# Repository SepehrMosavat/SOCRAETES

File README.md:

## SOCRAETES: SOlar Cells Recorded And EmulaTed EaSily

**Sayedsepehr Mosavat, Matteo Zella, Pedro José Marrón**  
**Networked Embedded Systems Group (NES) - Universität Duisburg-Essen**

SOCRAETES is a tool for supporting the design and evaluation of energy harvesting
systems. The core idea behind the development of SOCRAETES has been to
enable easy replication of the required hardware components, therefore
decreasing the entry-barrier into this field of research, even for researchers
and hobbyists that have little prior experience with electronics. This is
achieved by simplifying the hardware design as much as possible, and also by
employing only through-hole components in the required hardware.

The hardware design of SOCRAETES provides a high level of flexibility in terms
of the range of measurements and emulations. Since there is a tradeoff between
this range and the overall accuracy of the system, the users have the
possibility of modifying the underlying hardware by using different passive
components. By doing so, each user can target the best overall range of
measurements and emulation, while also achieving a high level of accuracy.

Please refer to our demo abstract, presented at EWSN 2021, for more information
regarding the design and implementation of SOCRAETES.

To use SOCRAETES, the following prerequisites exist:
- SOCRAETES hardware, either assembled on a prototyping board, or optionally,
using the PCB found in the hardware directory. Please note that the full
functionality of SOCRAETES can be realized using prototyping boards, but the
highest reliability and accuracy will be achieved only if the PCB is used.
Please refer to the hardware directory for instructions regarding preparing the
hardware
- SOCRAETES firmware, which will be running on a Teensy 3.6. Please refer to
the firmware directory for instructions on flashing the Teensy board.
- SOCRAETES software, which will be running on a host PC and used for
acquiring data and emulating traces. The current implementation of SOCRAETES
is using Python code, but we are working on extensions of this functionality
for further data visualization and analysis.

#### Contact us
In case you experience any issues while using SOCRAETES, or have any questions
or ideas for further improvements, please do not hesitate to contact us via
e-mail! You can find our contact information on our [web page](https://nes.uni-due.de).

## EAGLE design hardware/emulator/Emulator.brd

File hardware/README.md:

## SOCRAETES: SOlar Cells Recorded And EmulaTed EaSily

This document provides instructions for replicating the hardware of SOCRAETES.
As far as the hardware is concerned, there are 2 options for the users:
1. Using either a solderless breadboard or prototyping board (perfboard)
2. Using the SOCRAETES PCB

The SOCRAETES hardware could be implemented on a solderless breadboard, but this
is highly unrecommended, since the parasitic capacitance and inductance imposed
by a solderless breadboard will very likely interfere with the measurements and
the trace emulation. This will, in turn, reduce the overall accuracy and reliability
of the hardware. However, the SOCRAETES hardware can be implemented quite reliably
on a so-called *Perfboard*. In comparison to a solderless breadboard, a
perfboard will not only provide superior mechanical support to the components,
but also lower parasitic effects that could hinder the accuracy of the hardware.

Aside from the options mentioned above, the SOCRAETES hardware can also be
implemented on the dedicated PCB found in the hardware directory. This method will
yield the highest reliability and accuracy of the hardware, and therefore, is
the recommended method of replicating the hardware.

Regardless of the method chosen for implementing the SOCRAETES hardware, since
all of the components are available in through-hole packages, the soldering of
the hardware should not be a great challenge, even for the users with little
prior experience in electronics and soldering.

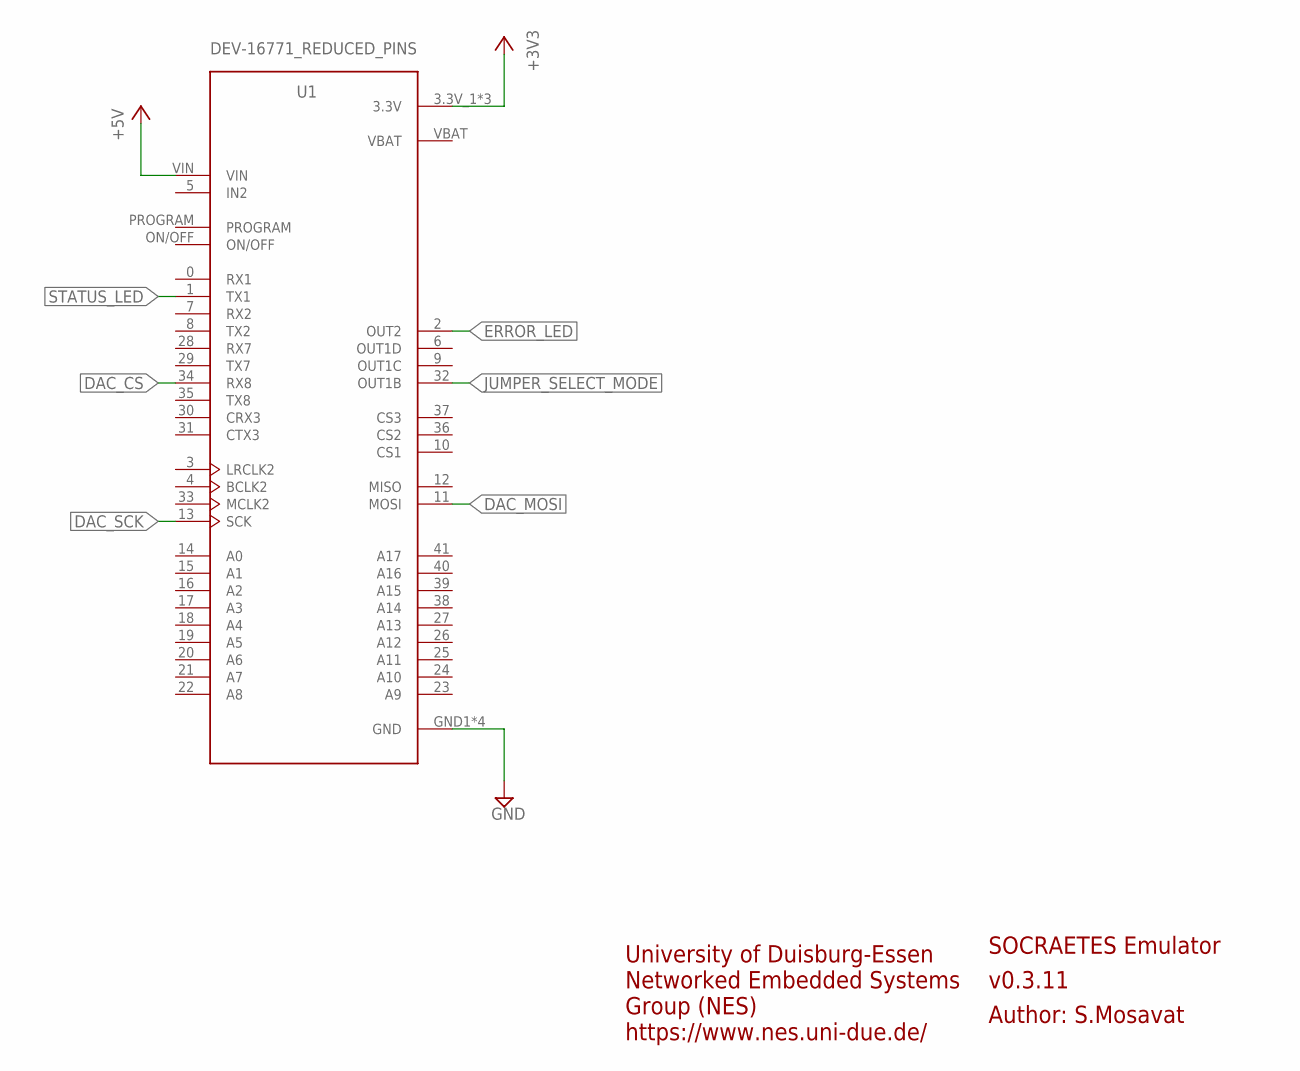
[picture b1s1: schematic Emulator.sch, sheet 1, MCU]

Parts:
U1: DEV-16771_REDUCED_PINS; MODULE_DEV-16771_REDUCED_PINS

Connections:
+3V3: U1.3.3V_1 (3.3V), U1.3.3V_2 (3.3V), U1.3.3V_3 (3.3V); also elsewhere on the board
+5V: U1.VIN; also elsewhere on the board
DAC_CS: U1.34 (RX8); also elsewhere on the board
DAC_MOSI: U1.11 (MOSI); also elsewhere on the board
DAC_SCK: U1.13 (SCK); also elsewhere on the board
ERROR_LED: U1.2 (OUT2); also elsewhere on the board
GND: U1.GND1 (GND), U1.GND2 (GND), U1.GND3 (GND), U1.GND4 (GND); also elsewhere on the board
JUMPER_SELECT_MODE: U1.32 (OUT1B); also elsewhere on the board
STATUS_LED: U1.1 (TX1); also elsewhere on the board

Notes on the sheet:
SOCRAETES Emulator
v0.3.11
Author: S.Mosavat
University of Duisburg-Essen Networked Embedded Systems Group (NES) https://www.nes.uni-due.de/

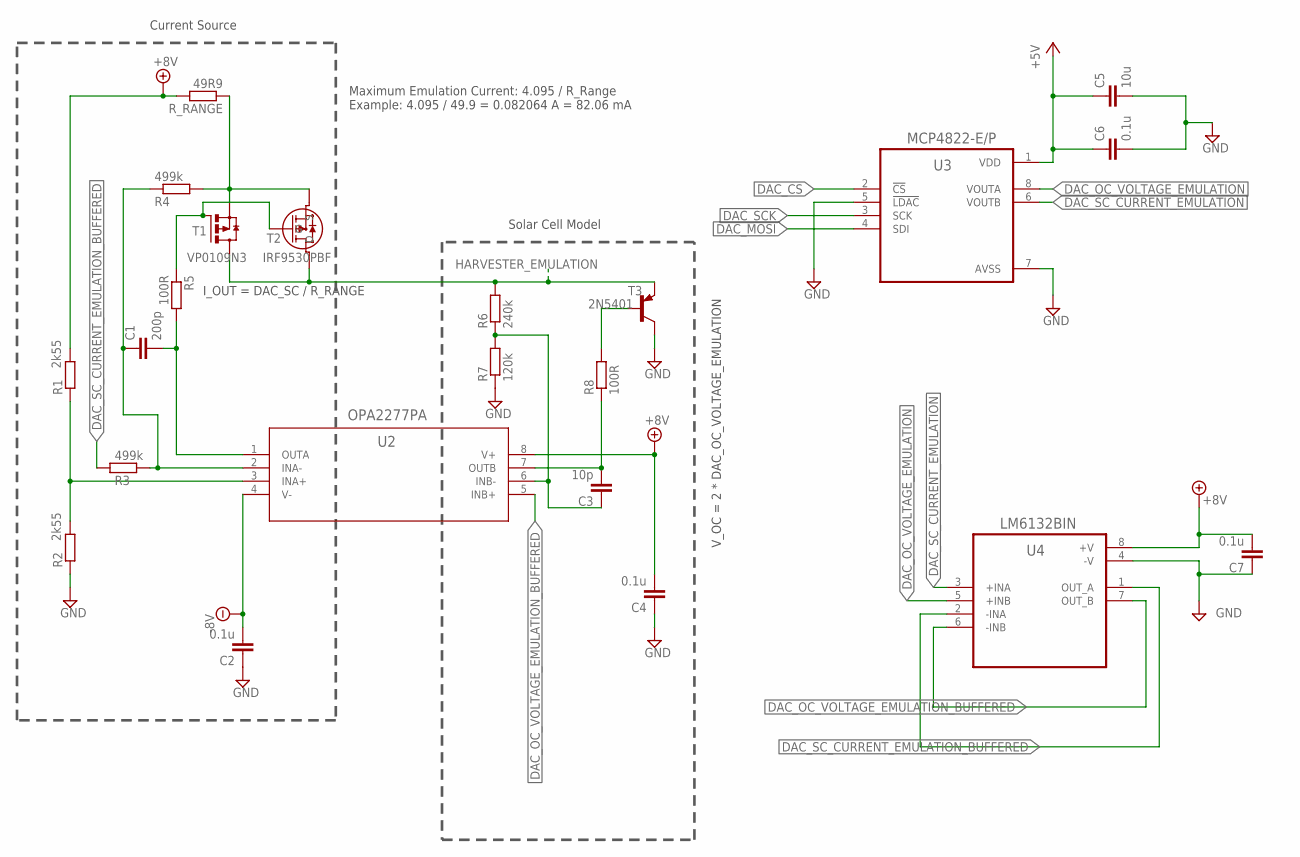
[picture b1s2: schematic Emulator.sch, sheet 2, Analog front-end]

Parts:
C1: 200p; C025-024X044
C2, C4, C6, C7: 0.1u; C025-024X044
C3: 10p; C025-024X044
C5: 10u; C025-024X044
R1, R2: 2k55; 0207/10
R3, R4: 499k; 0207/10
R5, R8: 100R; 0207/10
R6: 240k; 0207/10
R7: 120k; 0207/10
R_RANGE: 49R9; 0207/10
T1: VP0109N3; TO92-SGD
T2: IRF9530PBF; TO220AB_VIS
T3: 2N5401; TO92-EBC
U2: OPA2277PA; P8
U3: MCP4822-E/P; DIP787W46P254L927H533Q8
U4: LM6132BIN; DIP794W45P254L959H508Q8

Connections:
+5V: C5.1, C6.1, U3.1 (VDD); also elsewhere on the board
+8V: C4.2, C7.2, R1.2, R_RANGE.2, U2.8 (V+), U4.8 (+V); also elsewhere on the board
-8V: C2.2, U2.4 (V-); also elsewhere on the board
DAC_CS: U3.2 (!CS); also elsewhere on the board
DAC_MOSI: U3.4 (SDI); also elsewhere on the board
DAC_OC_VOLTAGE_EMULATION: U3.8 (VOUTA), U4.5 (+INB)
DAC_OC_VOLTAGE_EMULATION_BUFFERED: U2.5 (INB+), U4.6 (-INB), U4.7 (OUT_B)
DAC_SCK: U3.3 (SCK); also elsewhere on the board
DAC_SC_CURRENT_EMULATION: U3.6 (VOUTB), U4.3 (+INA)
DAC_SC_CURRENT_EMULATION_BUFFERED: R3.2, U4.1 (OUT_A), U4.2 (-INA)
GND: C2.1, C4.1, C5.2, C6.2, C7.1, R2.1, R7.1, T3.C, U3.5 (!LDAC), U3.7 (AVSS), U4.4 (-V); also elsewhere on the board
HARVESTER_EMULATION: R6.2, T1.DRAIN (D), T2.D, T3.E; also elsewhere on the board
unnamed: R1.1, R2.2, U2.3 (INA+)
unnamed: C1.1, R3.1, R4.2, U2.2 (INA-)
unnamed: R5.1, T1.GATE (G), T2.G
unnamed: C1.2, R5.2, U2.1 (OUTA)
unnamed: R4.1, R_RANGE.1, T1.SOURCE (S), T2.S
unnamed: C3.1, R6.1, R7.2, U2.6 (INB-)
unnamed: R8.2, T3.B
unnamed: C3.2, R8.1, U2.7 (OUTB)

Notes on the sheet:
Current Source
Solar Cell Model
Maximum Emulation Current: 4.095 / R_Range Example: 4.095 / 49.9 = 0.082064 A = 82.06 mA
I_OUT = DAC_SC / R_RANGE
V_OC = 2 * DAC_OC_VOLTAGE_EMULATION

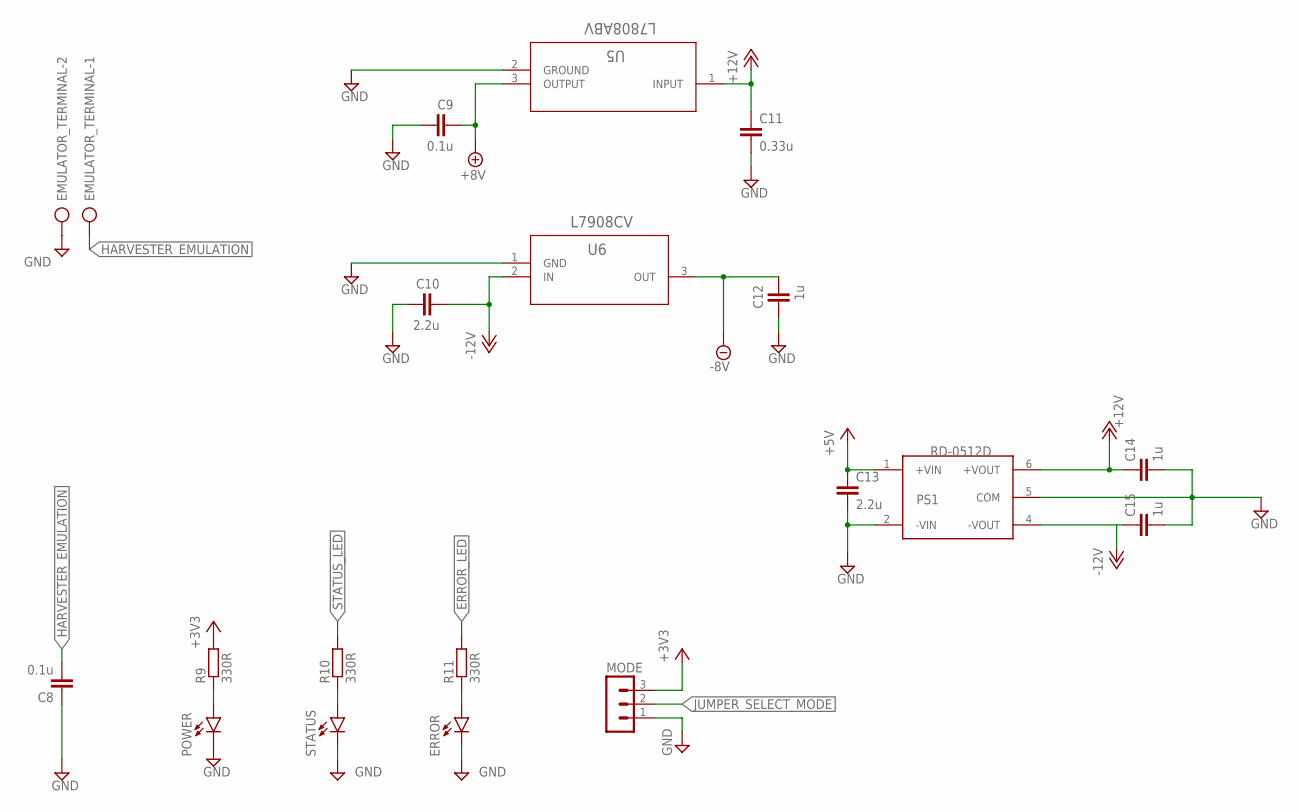
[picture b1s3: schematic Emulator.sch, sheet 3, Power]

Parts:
C8, C9: 0.1u; C025-024X044
C10, C13: 2.2u; C025-024X044
C11: 0.33u; C025-024X044
C12, C14, C15: 1u; C025-024X044
EMULATOR_TERMINAL: AK300/2
ERROR: LED5MM
MODE: MA03-1
POWER: LED5MM
PS1: RD-0512D; CONV_RD-0512D
R9, R10, R11: 330R; 0207/10
STATUS: LED5MM
U5: L7808ABV; TO-220_STM
U6: L7908CV; TO-220_STM

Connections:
+3V3: MODE.3, R9.2; also elsewhere on the board
+5V: C13.1, PS1.1 (+VIN); also elsewhere on the board
+8V: C9.2, U5.3 (OUTPUT); also elsewhere on the board
+12V: C11.1, C14.1, PS1.6 (+VOUT), U5.1 (INPUT)
-8V: C12.2, U6.3 (OUT); also elsewhere on the board
-12V: C10.2, C15.1, PS1.4 (-VOUT), U6.2 (IN)
ERROR_LED: R11.2; also elsewhere on the board
GND: C8.1, C9.1, C10.1, C11.2, C12.1, C13.2, C14.2, C15.2, EMULATOR_TERMINAL.2, ERROR.K (C), MODE.1, POWER.K (C), PS1.2 (-VIN), PS1.5 (COM), STATUS.K (C), U5.2 (GROUND), U6.1 (GND); also elsewhere on the board
HARVESTER_EMULATION: C8.2, EMULATOR_TERMINAL.1; also elsewhere on the board
JUMPER_SELECT_MODE: MODE.2; also elsewhere on the board
unnamed: R10.1, STATUS.A
unnamed: ERROR.A, R11.1
unnamed: POWER.A, R9.1
STATUS_LED: R10.2; also elsewhere on the board

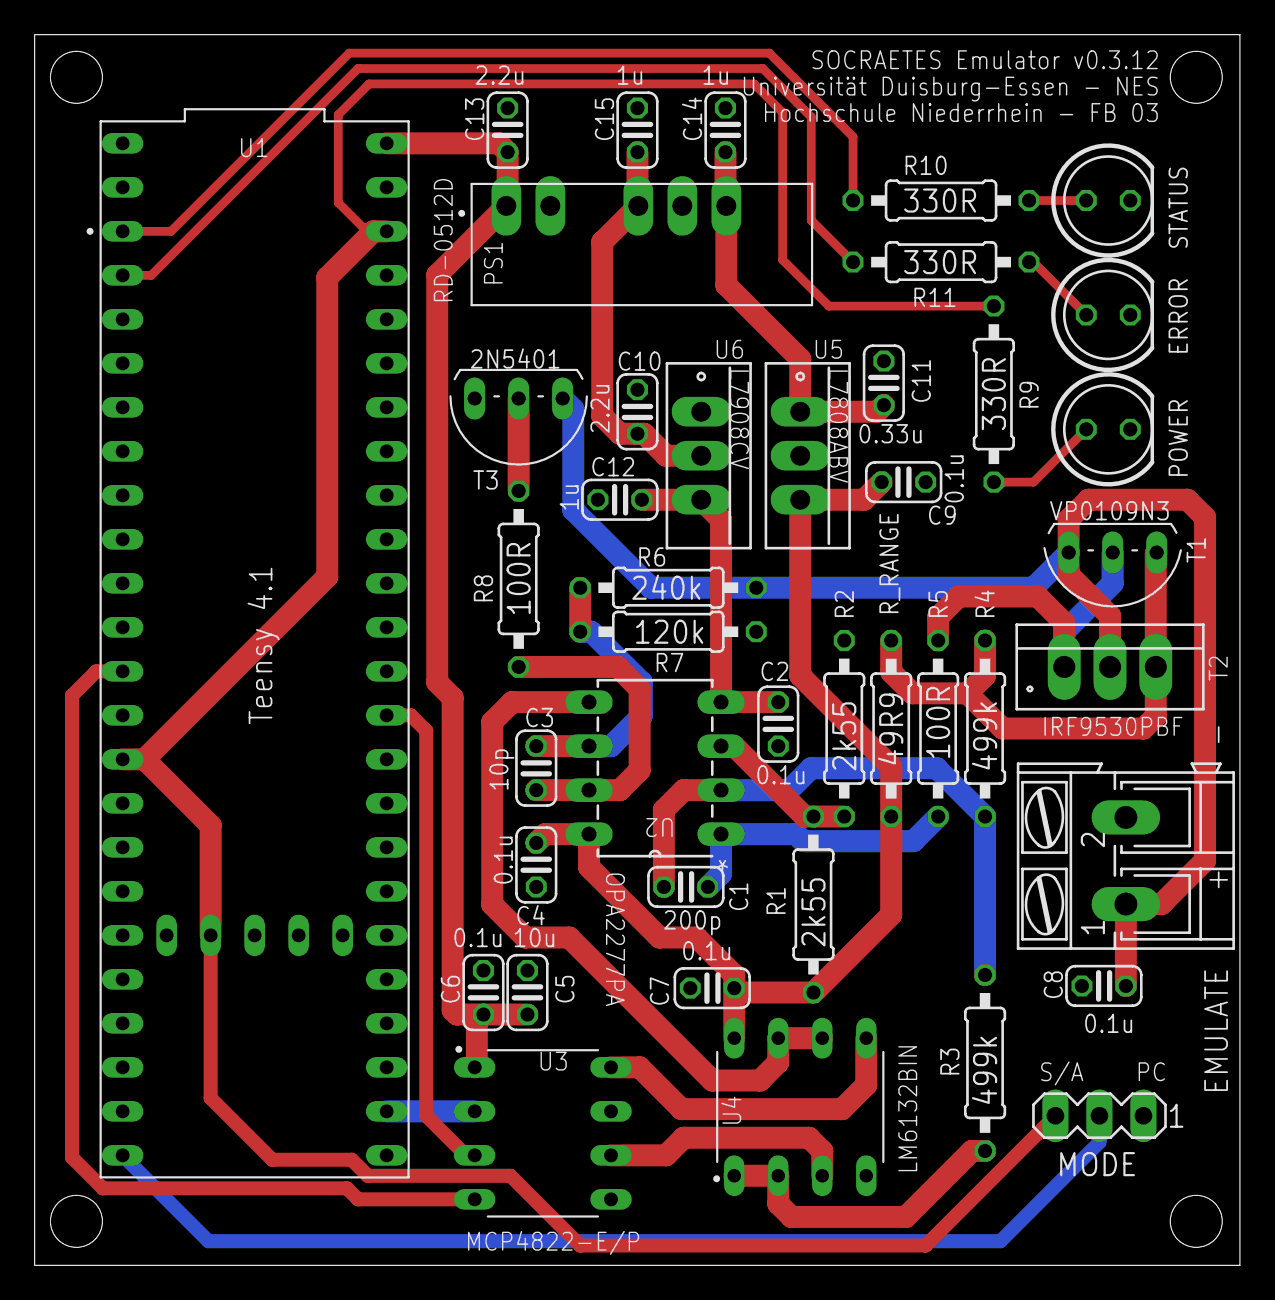
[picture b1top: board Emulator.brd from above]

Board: 2 copper layers, 69.6 x 71.0 mm, 42 parts (0 on the bottom side), 29 nets.

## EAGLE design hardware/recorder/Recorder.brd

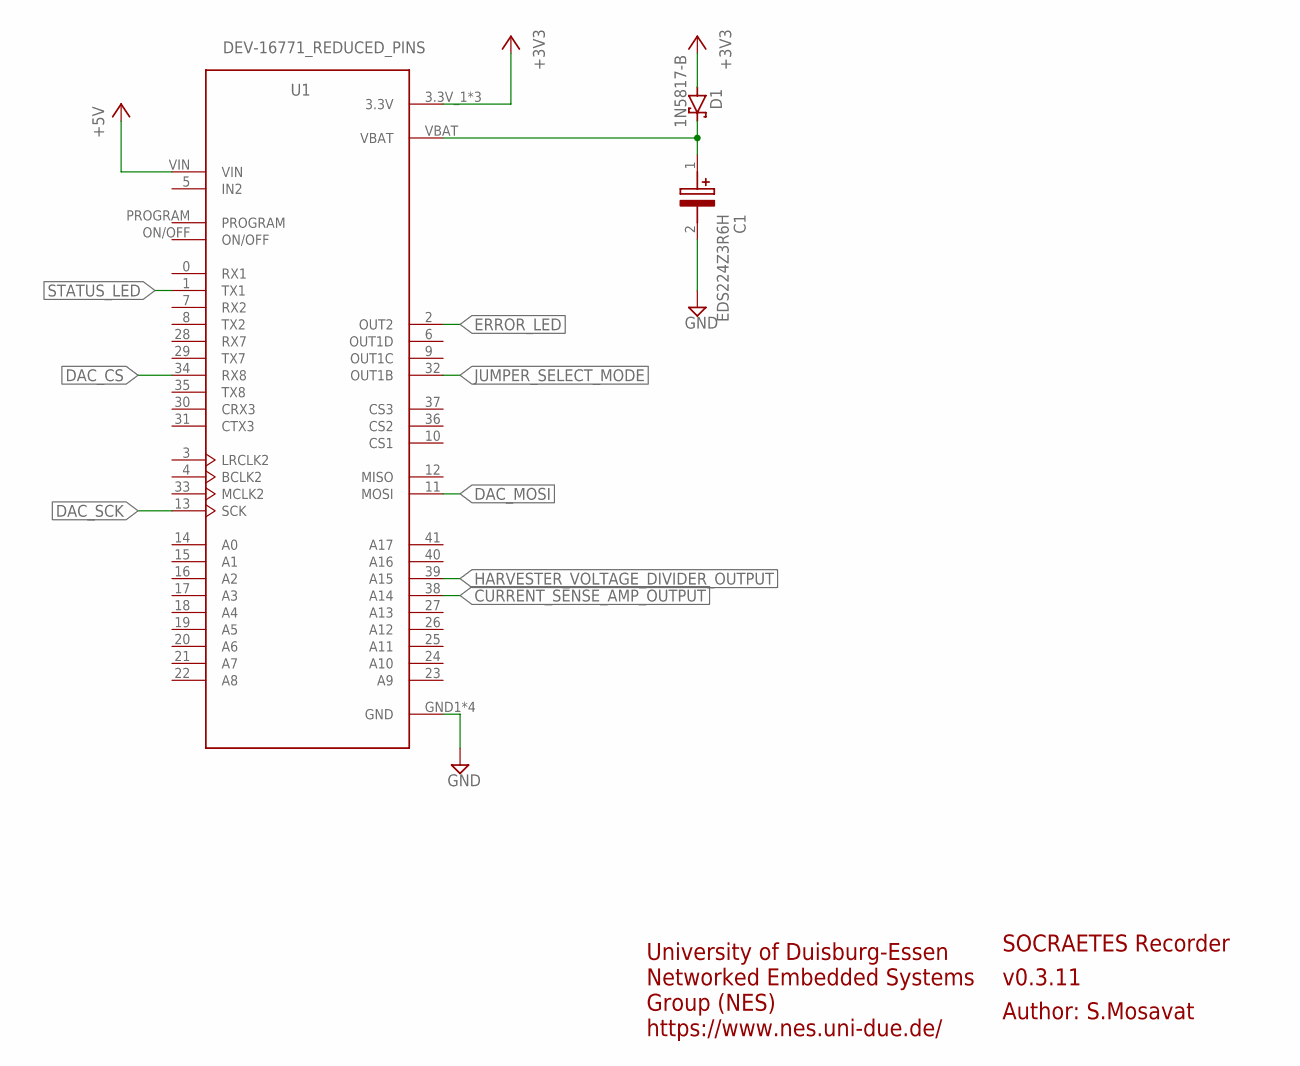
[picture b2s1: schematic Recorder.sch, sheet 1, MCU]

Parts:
C1: EDS224Z3R6H
D1: 1N5817-B; DO41-7.6
U1: DEV-16771_REDUCED_PINS; MODULE_DEV-16771_REDUCED_PINS

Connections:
+3V3: D1.A, U1.3.3V_1 (3.3V), U1.3.3V_2 (3.3V), U1.3.3V_3 (3.3V); also elsewhere on the board
+5V: U1.VIN; also elsewhere on the board
CURRENT_SENSE_AMP_OUTPUT: U1.38 (A14); also elsewhere on the board
DAC_CS: U1.34 (RX8); also elsewhere on the board
DAC_MOSI: U1.11 (MOSI); also elsewhere on the board
DAC_SCK: U1.13 (SCK); also elsewhere on the board
ERROR_LED: U1.2 (OUT2); also elsewhere on the board
GND: C1.2 (-), U1.GND1 (GND), U1.GND2 (GND), U1.GND3 (GND), U1.GND4 (GND); also elsewhere on the board
HARVESTER_VOLTAGE_DIVIDER_OUTPUT: U1.39 (A15); also elsewhere on the board
JUMPER_SELECT_MODE: U1.32 (OUT1B); also elsewhere on the board
unnamed: C1.1 (+), D1.C, U1.VBAT
STATUS_LED: U1.1 (TX1); also elsewhere on the board

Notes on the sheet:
SOCRAETES Recorder
v0.3.11
Author: S.Mosavat
University of Duisburg-Essen Networked Embedded Systems Group (NES) https://www.nes.uni-due.de/

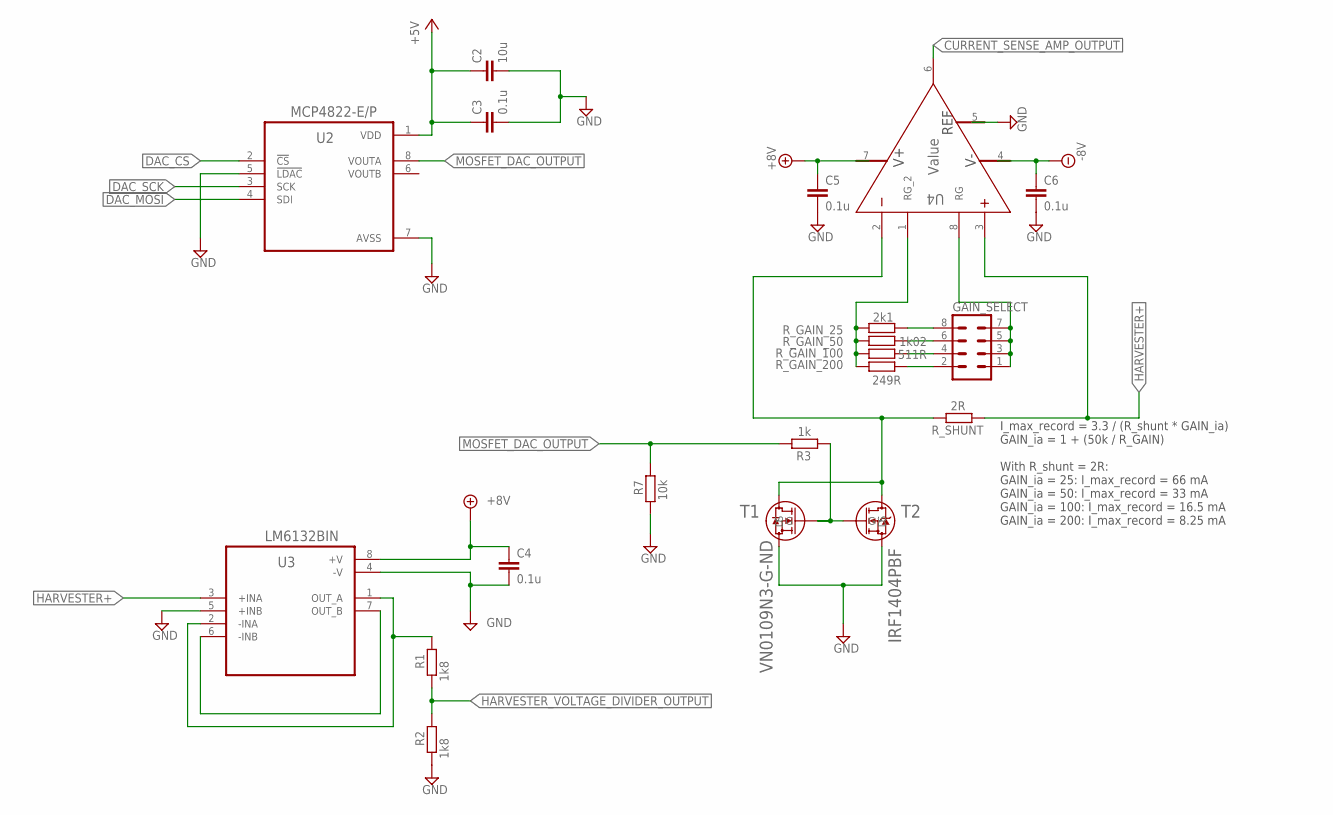
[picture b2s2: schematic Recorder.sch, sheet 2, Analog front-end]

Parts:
C2: 10u; C025-024X044
C3, C4, C5, C6: 0.1u; C025-024X044
GAIN_SELECT: MA04-2
R1, R2: 1k8; 0207/10
R3: 1k; 0207/10
R7: 10k; 0207/10
R_GAIN_25: 2k1; 0207/10
R_GAIN_50: 1k02; 0207/10
R_GAIN_100: 511R; 0207/10
R_GAIN_200: 249R; 0207/10
R_SHUNT: 2R; 0207/10
T1: VN0109N3-G-ND; TO92-CBE
T2: IRF1404PBF; PG-TO220-3-904_INF
U2: MCP4822-E/P; DIP787W46P254L927H533Q8
U3: LM6132BIN; DIP794W45P254L959H508Q8
U4: Value; P0008A

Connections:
+5V: C2.1, C3.1, U2.1 (VDD); also elsewhere on the board
+8V: C4.1, C5.1, U3.8 (+V), U4.7 (V+); also elsewhere on the board
-8V: C6.1, U4.4 (V-); also elsewhere on the board
CURRENT_SENSE_AMP_OUTPUT: U4.6 (OUT); also elsewhere on the board
DAC_CS: U2.2 (!CS); also elsewhere on the board
DAC_MOSI: U2.4 (SDI); also elsewhere on the board
DAC_SCK: U2.3 (SCK); also elsewhere on the board
GND: C2.2, C3.2, C4.2, C5.2, C6.2, R2.1, R7.1, T1.SOURCE (S), T2.S, U2.5 (!LDAC), U2.7 (AVSS), U3.4 (-V), U3.5 (+INB), U4.5 (REF); also elsewhere on the board
HARVESTER+: R_SHUNT.1, U3.3 (+INA), U4.3 (IN+); also elsewhere on the board
HARVESTER_VOLTAGE_DIVIDER_OUTPUT: R1.1, R2.2; also elsewhere on the board
MOSFET_DAC_OUTPUT: R3.2, R7.2, U2.8 (VOUTA)
unnamed: GAIN_SELECT.8, R_GAIN_25.1
unnamed: GAIN_SELECT.6, R_GAIN_50.1
unnamed: U3.6 (-INB), U3.7 (OUT_B)
unnamed: R_SHUNT.2, T1.DRAIN (D), T2.D, U4.2 (IN-)
unnamed: R1.2, U3.1 (OUT_A), U3.2 (-INA)
unnamed: GAIN_SELECT.4, R_GAIN_100.1
unnamed: R3.1, T1.GATE (G), T2.G
unnamed: R_GAIN_25.2, R_GAIN_50.2, R_GAIN_100.2, R_GAIN_200.2, U4.1 (RG_2)
unnamed: GAIN_SELECT.1, GAIN_SELECT.3, GAIN_SELECT.5, GAIN_SELECT.7, U4.8 (RG)
unnamed: GAIN_SELECT.2, R_GAIN_200.1

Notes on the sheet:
I_max_record = 3.3 / (R_shunt * GAIN_ia) GAIN_ia = 1 + (50k / R_GAIN) With R_shunt = 2R: GAIN_ia = 25: I_max_record = 66 mA GAIN_ia = 50: I_max_record = 33 mA GAIN_ia = 100: I_max_record = 16.5 mA GAIN_ia = 200: I_max_record = 8.25 mA

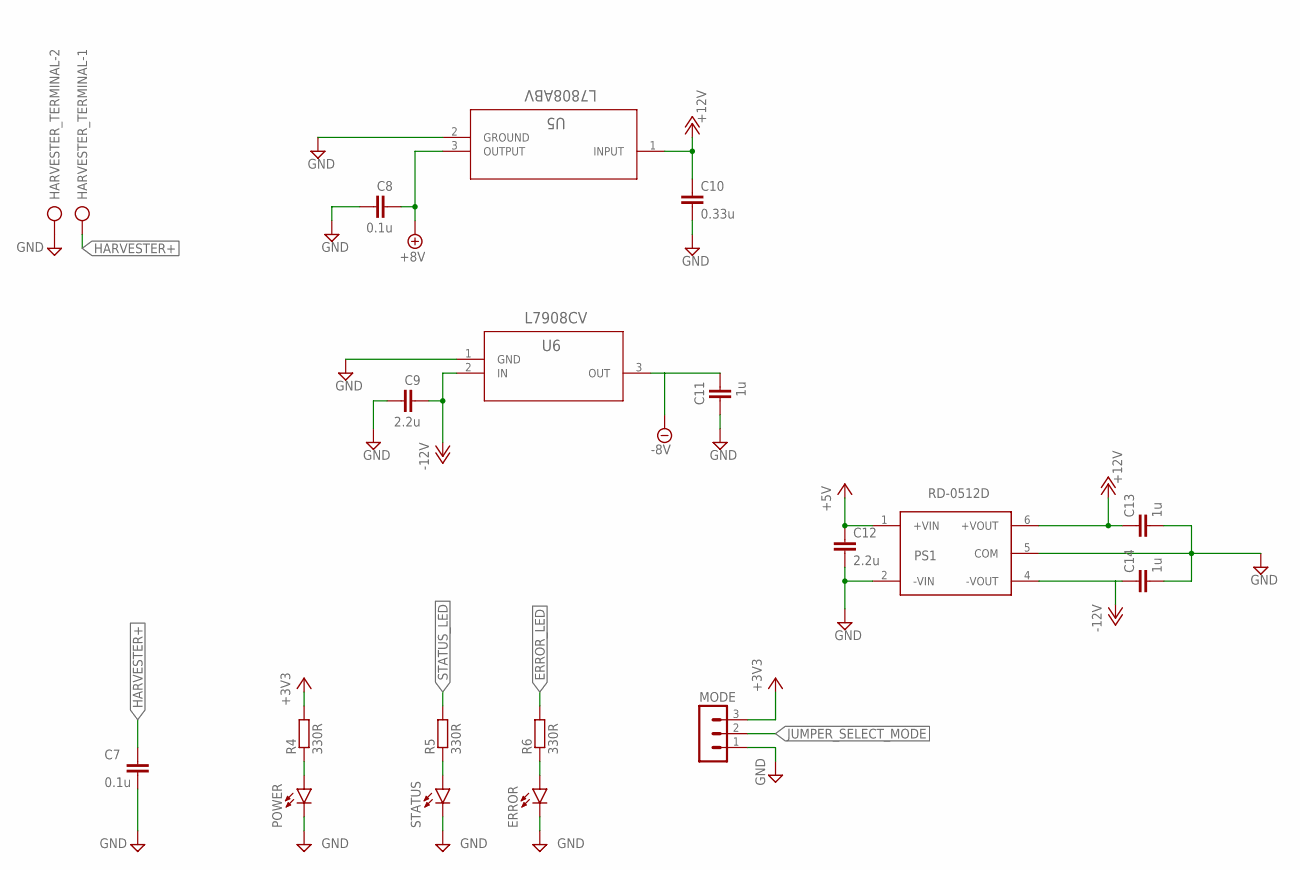
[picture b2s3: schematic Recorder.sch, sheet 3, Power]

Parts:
C7, C8: 0.1u; C025-024X044
C9, C12: 2.2u; C025-024X044
C10: 0.33u; C025-024X044
C11, C13, C14: 1u; C025-024X044
ERROR: LED5MM
HARVESTER_TERMINAL: AK300/2
MODE: MA03-1
POWER: LED5MM
PS1: RD-0512D; CONV_RD-0512D
R4, R5, R6: 330R; 0207/10
STATUS: LED5MM
U5: L7808ABV; TO-220_STM
U6: L7908CV; TO-220_STM

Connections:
+3V3: MODE.3, R4.2; also elsewhere on the board
+5V: C12.1, PS1.1 (+VIN); also elsewhere on the board
+8V: C8.2, U5.3 (OUTPUT); also elsewhere on the board
+12V: C10.1, C13.1, PS1.6 (+VOUT), U5.1 (INPUT)
-8V: C11.2, U6.3 (OUT); also elsewhere on the board
-12V: C9.2, C14.1, PS1.4 (-VOUT), U6.2 (IN)
ERROR_LED: R6.2; also elsewhere on the board
GND: C7.2, C8.1, C9.1, C10.2, C11.1, C12.2, C13.2, C14.2, ERROR.K (C), HARVESTER_TERMINAL.2, MODE.1, POWER.K (C), PS1.2 (-VIN), PS1.5 (COM), STATUS.K (C), U5.2 (GROUND), U6.1 (GND); also elsewhere on the board
HARVESTER+: C7.1, HARVESTER_TERMINAL.1; also elsewhere on the board
JUMPER_SELECT_MODE: MODE.2; also elsewhere on the board
unnamed: ERROR.A, R6.1
unnamed: R5.1, STATUS.A
unnamed: POWER.A, R4.1
STATUS_LED: R5.2; also elsewhere on the board

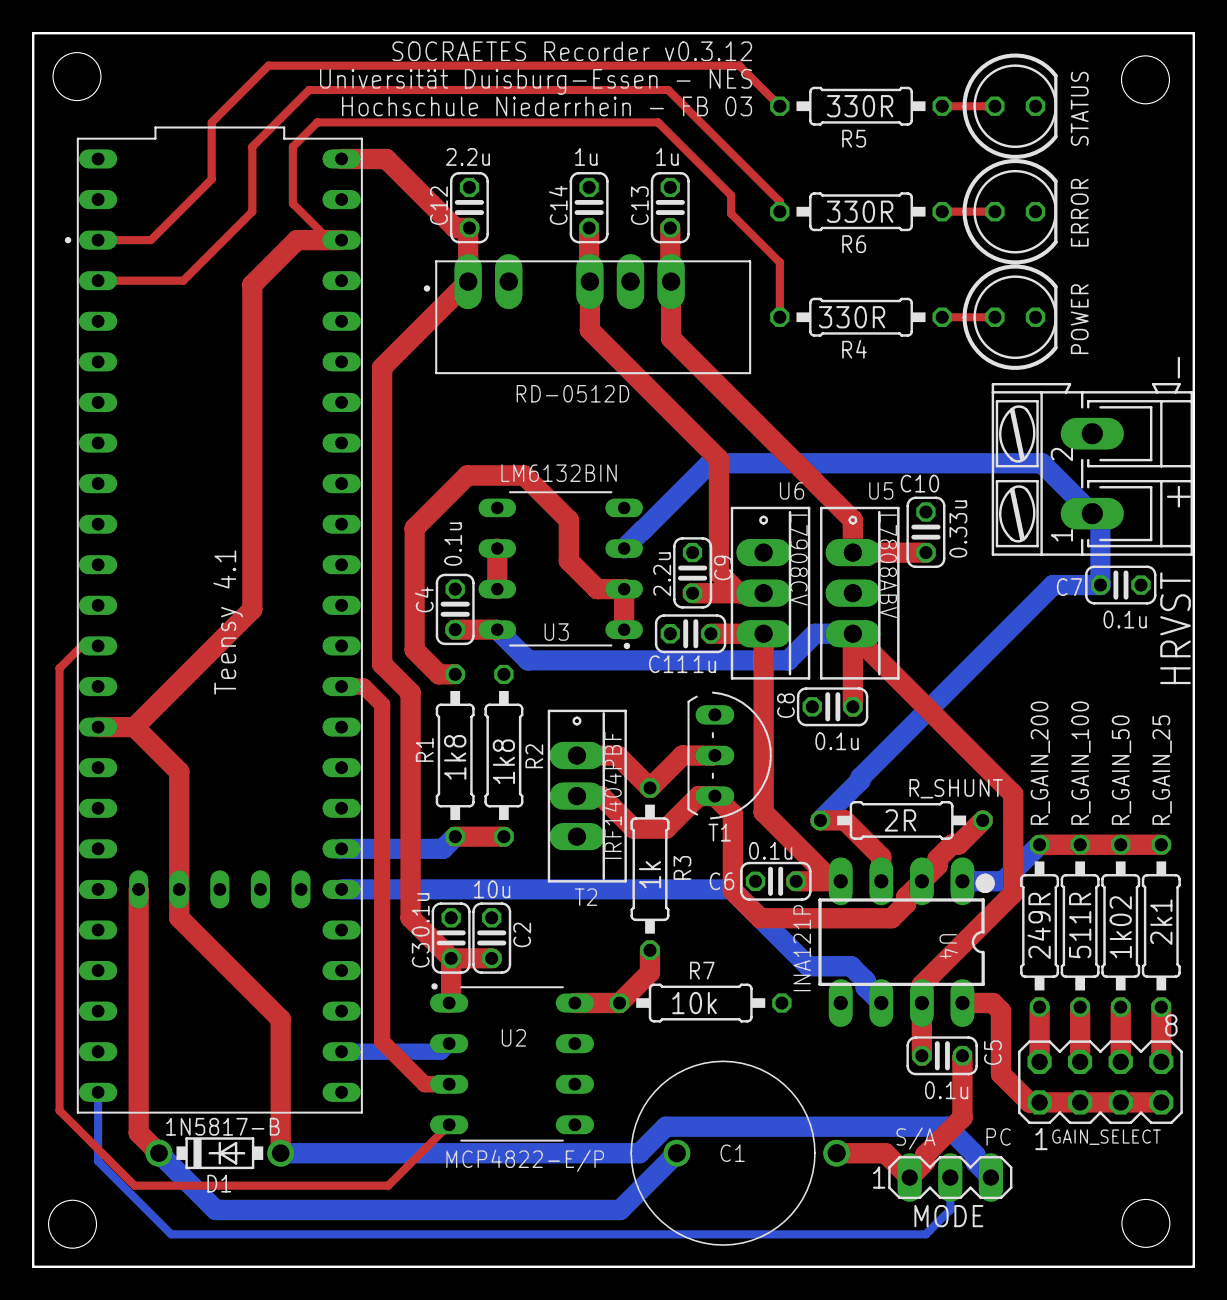
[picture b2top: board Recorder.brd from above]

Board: 2 copper layers, 72.6 x 77.2 mm, 42 parts (0 on the bottom side), 31 nets.

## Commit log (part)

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2020-09-17 Update gitignore
2020-09-17 Add microcontroller firmware files
2020-09-17 Add software files
2020-09-17 Add hardware readme file
2020-09-17 Move solar cell recorder files to a separate folder
2020-09-17 Update ADC reference voltage definition
2020-09-17 Increase PGA's gain used for current measurement
2020-09-17 Add class member for the number of points in each curve
2020-09-17 Decrease PGA's gain used for current measurement to avoid saturation issues at high currents
2020-09-17 Add delay after writing a new value to the potentiometer
2020-09-17 Refactor code
2020-09-17 Change the number of captured points in each curve
2020-09-17 Stop tracking IDE files
2020-09-17 Change the path of recorded traces to a separate directory
2020-09-17 Remove delay to achieve higher capture speed
2020-09-17 Specify data type in the HDF5 file containing the captured traces
2020-09-17 Add class for describing the energy harvesting conditions
2020-09-17 Add a feature for automated filename generation
2020-09-18 Add TODO
2020-09-18 Add return type to the function
2020-09-18 Add error checking for empty folder
2020-09-18 Add the start date and time of data capturing to the harvesting condition
2020-09-21 Add the end time of data capturing to the harvesting condition
2020-09-25 Add check for negative ADC readings for current and voltage calculations
2020-10-01 Add/edit readme files
2020-10-01 Dynamically update the plot range
2020-10-15 Remove DAC and rotary encoder from the current project
2020-10-15 Replace digital potentiometer as system load with a MOSFET controlled by the DAC
2020-10-15 Add function for updating the MOSFET load on each main loop iteration
2020-10-15 Change the value of the resistors in the voltage divider used for measuring the harvester voltage
2020-10-15 Reduce ADC resolution
2020-10-15 Modify ADC settings for improving the quality of current/voltage measurements
2020-10-15 Update definitions used in function implementation
2020-10-15 Remove PGA gain from function arguments
2020-10-15 Use single-ended ADC input instead of differential inputs for harvester current measurements
2020-10-15 Add new pins
2020-10-15 Remove "capture status" pins since this functionality is no longer needed
2020-10-15 Use 16-bit ADC resolution for current measurements
2020-10-15 Modify shunt resistor and current sense amplifier gain to achieve better accuracy over a wider measurement range
2020-10-16 Increase delay for improved debug mode outputs
2020-10-16 Add another shunt resistor for measuring smaller, low-current output harvesters
2020-10-22 Add new look-up table for the load MOSFET
    The higher DAC voltage results in a lower drain-source ON-state resistance
2020-12-07 Update repository name and project structure
2021-01-13 Add 15 seconds of delay at the startup
    This delay serves as a solution for the serial communication
    issues on Linux systems. The delay will be signaled to the user
    by utilizing the on-board LED.
2021-01-18 Implement the emulator software
2021-01-18 Add data type for selecting the debugging mode
2021-01-18 Add debugging modes
2021-01-19 Reformat code
2021-01-19 Change the default hdf5 file name
2021-01-19 Optimize imports
2021-01-19 Get harvesting conditions from function argument
2021-01-19 Add function argument to allow the user to provide a file name
2021-01-19 Add event for thread synchronization
    The event will notify the thread to stop at the end of program execution.
2021-01-19 Remove unused class
2021-01-19 Add function argument for getting the serial port
2021-01-19 Add command line interface
2021-01-19 Add function for handling SIGINT for terminating the program
2021-01-19 Implement timer thread for measuring the data capture duration
2021-01-19 Remove old code
2021-01-19 Start threads in the main function after getting the CLI parameters from the user
2021-01-19 Implement emulator firmware
2021-01-19 Rename entry points
2021-01-19 Add docstrings
2021-01-21 refactor: updated setup for linux
2021-01-24 refactor: removed main.py for easier master branch merge later
2021-01-24 feat: added socketio example, logging
2021-01-24 feat: implemented curve transmit from SOCRAETES to remote backend
2021-01-30 feat: added script to accelerate recorder startup
2021-02-02 Add hardware CAD files
2021-02-11 Remove virtual environment from the repo
2021-02-11 Add requirements.txt
2021-02-16 Update documentation
2021-02-16 Add emulator BOM
2021-02-16 Update recorder hardware
2021-02-16 Add recorder BOM
2021-02-16 Substitute magic number with a definition
2021-02-16 Add definition for the emulator range resistor
2021-02-16 Add gain equation for the instrumentation amplifier
2021-02-16 Update current sense shunt resistor value
2021-02-16 Add definitions for a variety of instrumentation amplifier gain values
2021-02-17 Correct board version on the silkscreen
2021-03-08 Add vias, fix ground pour on the top layer
2021-03-08 Fix ADC pins for the PCB
2021-03-08 Increase ADC resolution
2021-03-08 Use maximum ADC sampling and conversion speed
2021-03-08 Decrease the delay between each curve to increase the overall curve capturing speed
2021-04-26 Fix DAC pin numbers
2021-04-26 Add offset for calibration of the DAC output for short-circuit current emulation
2021-04-26 Toggle the LED on each emulated curve to provide the user a visual cue
2021-04-26 Remove explicit baud rate notation for the serial library since this will have no effect when the connection is over USB
2021-04-26 Change the gain of the IA to 99 for the current board
2021-04-26 Use a new LUT for capturing the IV curves.
    The new LUT exhibits a better performance over the entire range of current measurement.
2021-04-26 Add calibration offsets and check the return value to make sure it is not negative
2021-04-26 Add a capacitor to the solar cell model op amp for stability of the op amp's output
2021-04-26 Improve the format and readability of the information printed during emulation
2021-04-26 Add PCB v0.1.2 images
2021-05-26 Use the logging library for outputting information and debug messages
2021-05-26 Fix maximum sequence number of the points in each curve
2021-05-26 Fix the issue with the inconsistent number of points in each curve
2021-05-26 Add a feature for emulating an intermittent power source with adjustable power on/off cycles
    This is an experimental feature and is not meant for normal use.
2023-04-04 Add platformio.ini in recorder and emulator
2023-04-04 Change src_dir variable in platformio.ini
2023-04-06 Reduce delay
2023-04-06 Add minor changes to the schematics
2023-04-06 Fix timing issue with disk commits
2023-04-06 Fix bug in curve point sequence numbers
2023-04-21 add bug fix if captured_traces directory doesn't exists
2023-04-21 changed to work with latest library
2023-04-21 Change calculation of CURRENT_SENSE_AMPLIFIER_GAIN to floating point
2023-04-21 Lower maximum number of filenames
2023-04-21 Add shebang in record.py and make it executable
2023-04-21 Make path for captured traces os independent
2023-04-23 added comments, changed python version on shebang, code was made more os independent
2023-04-24 Add Time library for TimeLib.h
2023-04-24 Fix config_file reading
2023-04-24 Change timing mechanism
2023-04-25 Change data type of sequence number
2023-04-25 Fix typo, change cycle time, ivCurveSequenceNumber handling,
2023-04-25 Calculate end_timestamp_s just once in createNewFile
2023-04-25 Change uartByteArray from extern to static
2023-04-26 fixed configuration file read in
2023-04-27 Add check for dos or unix line endings when reading config
2023-04-27 Create byte array only when needed and change cycle time
2023-04-27 Migrate recorder board to Teensy 4.1
2023-04-27 Update pin mappings
2023-04-27 Update reference voltages
2023-04-27 Add MCP4822 DAC
2023-04-27 Update startup delay function
2023-04-27 Decrease ADC resolution to 12 bits for Teensy 4.1
2023-04-27 Add MCP4822 DAC library
2023-04-27 Update Platformio environment
2023-04-27 Use the status LED instead of the built-in one
2023-04-27 Update current and voltage readings with the ADC
2023-04-27 Add debug information for the calibration mode
2023-04-27 Update the LUT for load MOSFET gate voltages during load sweep with MCP4822
2023-04-27 Write to SD card if available or restart
2023-04-27 Change config file line numbers
2023-04-27 Add resistor for gain=200
2023-04-27 Increase shunt resistor to 2R
2023-04-27 Fix amplifier gain calculation
2023-04-27 Move source code to .\src directory
2023-04-27 Update gain resistor
2023-04-27 Move supercapacitor
2023-04-28 Implement new timing mechanism
2023-04-28 Do not activate CALIBRATION_MODE automatically when DEBUG_MODE is active
2023-04-28 Make ADC a local variable, change timing in DEBUG_MODE
2023-04-28 Make byte array a function local variable
2023-04-28 Make ivCurveSequenceNumber a local variable
2023-05-03 Switch timing to elapsedMillis to handle roll over
2023-05-03 Change data type of MaxTaskTime_ms
2023-05-03 Include elapsedMillis.h
2023-05-03 Correct format specifier for unsigned long
2023-05-16 Migrate emulator firmware to Teensy 4.1
2023-05-16 Update emulator current range resistor
2023-05-16 Reduce ADC resolution to 10 bits
2023-05-16 Add error LED
2023-05-16 Add minor changes to the hardware
2023-05-17 restored status led functionality
2023-05-22 Update resistor values
2023-05-22 Update info text
2023-05-24 add jumper usability instead of precompiler options for S/A and PC mode
2023-05-24 Update board version
2023-05-24 Add new recorder MOSFET and update the existing one
2023-05-25 include emulator sd mode and emulator jumper functionality
2023-05-25 add error led functionality
2023-05-26 fix function declaration bug
2023-05-31 change default duration time to forever
2023-06-01 first state of CTS implementation
2023-06-01 add flag for cts so that only one cts is send as queue is empty
2023-06-07 make pc transmission 2x faster
2023-06-09 make some minor speed improvements
2023-06-14 fix bugs
2023-06-22 adding automatically adjusted mosfet values
2023-06-22 change mosfet calibration intervall and fix bugs
2023-06-22 fix some small matplotlib bugs
2023-06-28 fix plot surface bug and delete data with not up to date structure
2023-06-29 preperation for rtd+ sphinx documentation
2023-06-29 Create Makefile for documentation (sphinx)
2023-06-30 move old documentation to read the docs
2023-06-30 add code language support
2023-06-30 add toctree
2023-06-30 modify docu files
2023-07-11 Add MCP48xx library as dependency
2023-07-11 Update resistor value
2023-07-12 Readd MCP48xx library because of SPI bug
2023-07-12 Add LUT for the IRF1404 MOSFET
2023-08-01 Replace dynamic memory allocation by reading file line by line
2023-08-01 Add example file for emulation and describe usage with SD-card
2023-08-21 small docu changes
2023-08-21 test new toctree
2023-08-21 change format
2023-08-21 test rtd syntax
2023-08-22 Refactor recorder
2023-08-22 test block syntax
2023-08-23 change recorder layout to be more simple
2023-08-24 added docu for recorder firmware
2023-08-24 change rtd synatx
2023-08-24 add firmware emulator sd mode docu
2023-08-24 first firmware and index docu version
2023-08-24 trying rtd bullet point syntax
2023-08-24 add images for hardware documentation
2023-08-30 syntax changes
2023-08-30 change syntax
2023-10-05 Remove unnecessary path declaration in platformio.ini
2023-10-25 Remove access to LED_BUILTIN as it is used for SPI
2023-10-25 Remove access to LED_BUILTIN
2023-11-01 Change voltage limit in CalculateMosfetValue(), for faster convergence
2023-11-15 Implement sigmoid function to search mosfet values
2023-11-21 Add function description
2023-11-28 Add sleep functionality with Snooze library
2023-12-05 Turn on STATUS LED during measuring
2023-12-06 Add bug fix explanation, with links for reference
2023-12-08 First reliably working version
2023-12-08 Move DAC to functions
2023-12-20 Correct for loop counter
2023-12-20 Fix counters
2024-01-12 Working state
2024-01-15 Turn off serial if not necessary
2024-01-31 Version without switch
2024-04-23 Update platformio.ini files
2024-06-12 Make emulator file reading more robust
2024-06-21 Refactor and startup boost in setupSD
2024-09-01 Implement simple power cycle emulator

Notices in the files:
parts and their libraries:
COPYRIGHT: Copyright (C) 2023 Ultra Librarian. All rights reserved.
